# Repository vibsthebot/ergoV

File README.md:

# ergoV

A custom ergonomic split keyboard powered by a nrf52840 and PG1316S switches. At under 8 millimeters thick, this keyboard is extremly thin and portable. 

## Features
* Battery Charging
* USB C
* Bluetooth

## PCB 

## Schematic

Designed in [KiCAD](https://kicanvas.org/?github=https%3A%2F%2Fgithub.com%2Fvibsthebot%2FergoV%2Ftree%2Fmain%2Fsrc%2Fleft) and [Onshape](https://cad.onshape.com/documents/23d341e5ba1096076f5e498a/w/17b9fcd4bdbd13d07aada607/e/fd0f7eacd049861961437f33?renderMode=0&uiState=68cac4ba1e18efa2742f181c)

## BOM

| Item                                    | Quantity | Link                                                                                                         | Price (each) |
|------------------------------------------|----------|--------------------------------------------------------------------------------------------------------------|--------------|
| 301540 batteries                        | 2        | [AliExpress](https://www.aliexpress.com/i/2255800173650652.html)                                             | $6.10        |
| PCB (JLCPCB)                            | 2        | -                                                                                                            | $8.40        |
| LCSC parts                              | -        | -                                                                                                            | $50.00       |
| PG1316S switches (10 pack)              | 4 packs  | [HolyKeebs](https://holykeebs.com/products/kailh-pg1316s-butterfly-switch-10-pack)                           | $7.50        |
| PG1316S keycaps (10 pack)               | 4 packs  | [HolyKeebs](https://holykeebs.com/products/kailh-pg1316s-keycaps)                                            | $4.50        |
| **Total**                               |          |                                                                                                              | **$129.60**  |

**Total estimated cost:** $129.60

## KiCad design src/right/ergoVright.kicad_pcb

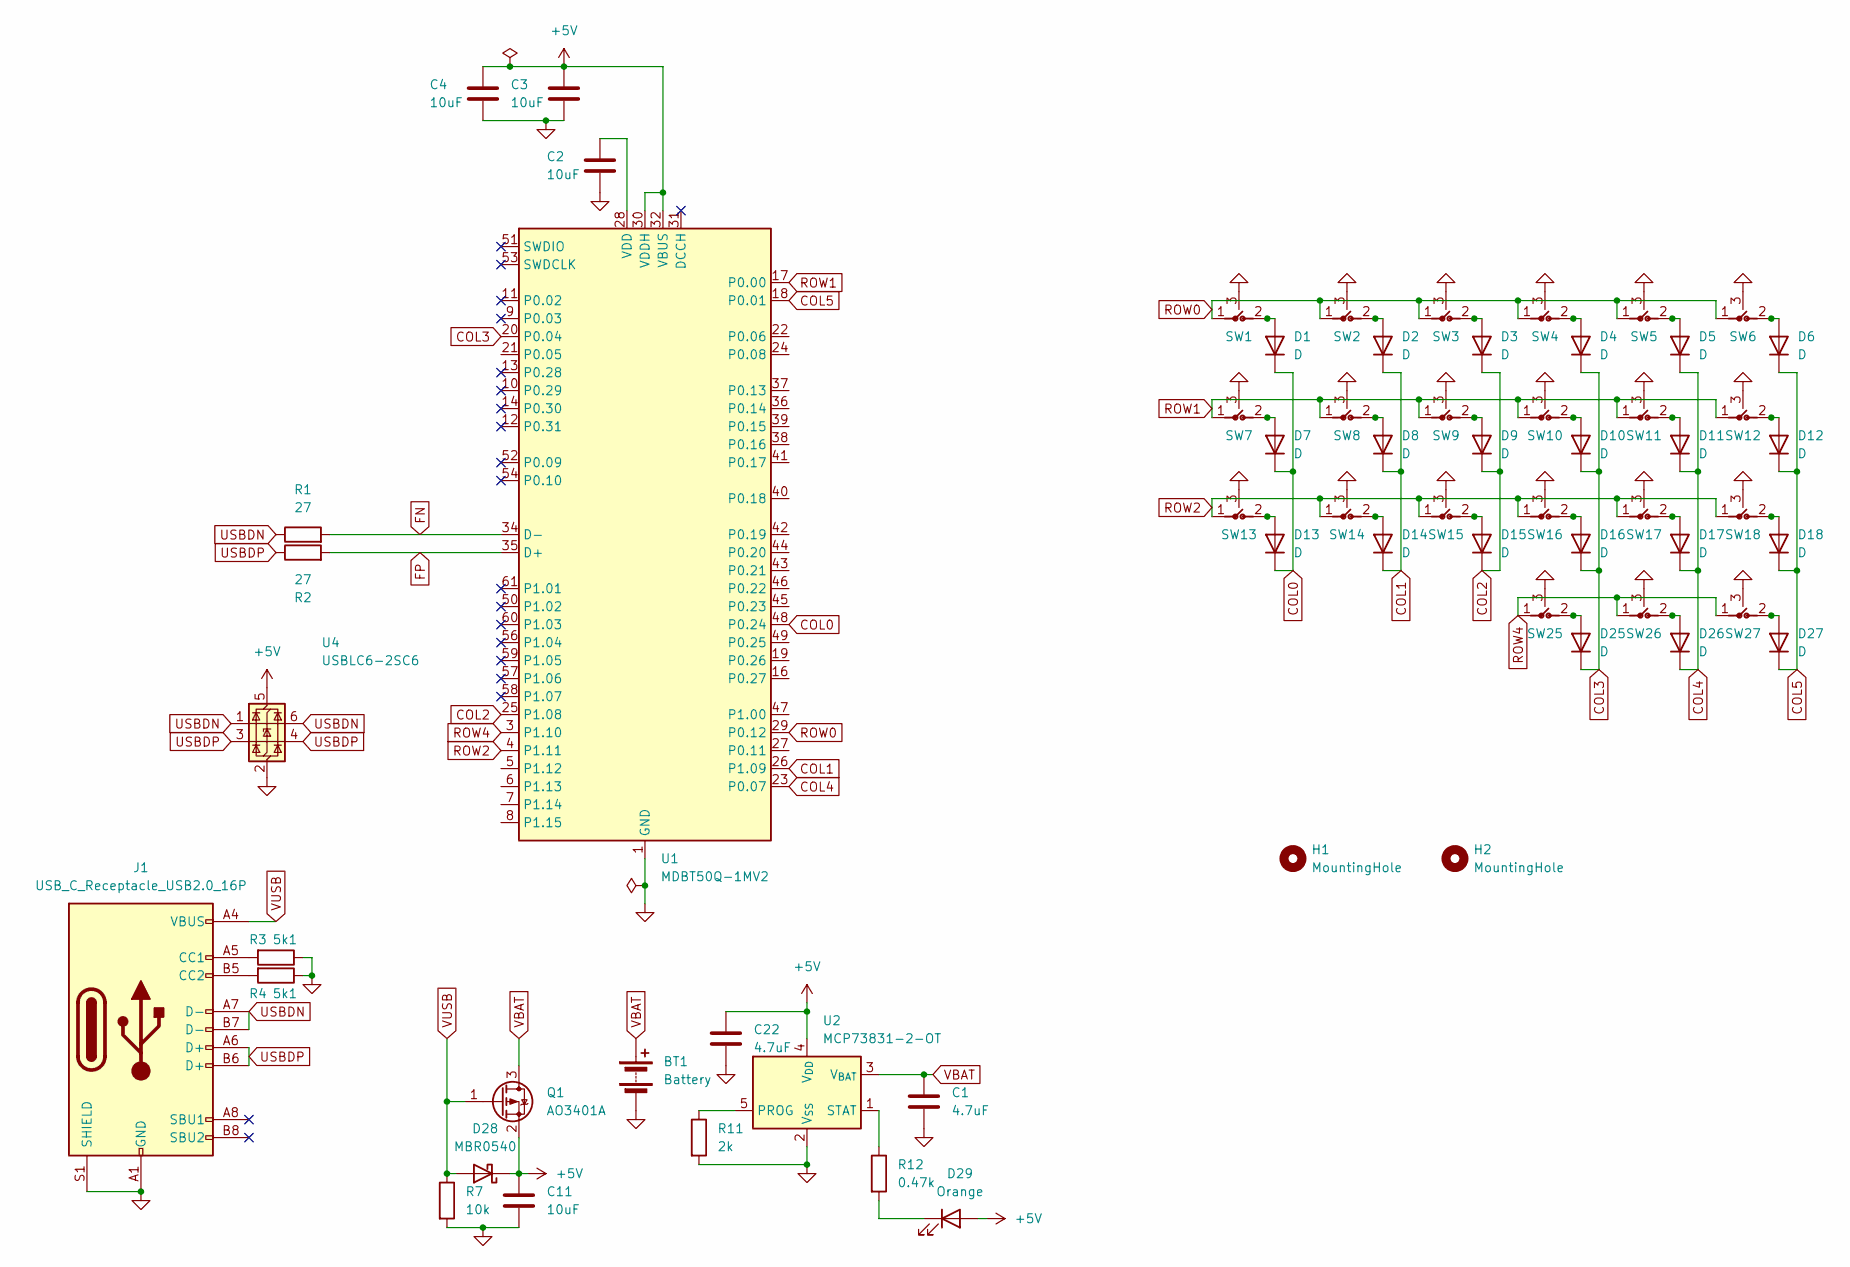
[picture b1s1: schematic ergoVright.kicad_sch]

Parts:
BT1: Battery; JST_PH_S2B-PH-K_1x02_P2.00mm_Horizontal
C1, C22: 4.7uF; C_0603_1608Metric; LCSC C19666
C2, C3, C4, C11: 10uF; C_0603_1608Metric; LCSC C19702
D1, D2, D3, D4, D5, D6, D7, D8, D9, D10, D11, D12, D13, D14, D15, D16, D17, D18, D25, D26, D27: D; Diode_SOD-123; LCSC C81598
D28: MBR0540; D_SOD-123; LCSC C77337
D29: Orange; LED_0805_2012Metric; LCSC C434437
H1, H2: MountingHole; MountingHole_2.7mm_M2.5
J1: USB_C_Receptacle_USB2.0_16P; USB_C_Receptacle_G-Switch_GT-USB-7010ASV; LCSC C67380
Q1: AO3401A; SOT-23; LCSC C306862
R1, R2: 27; R_0402_1005Metric; LCSC C25100
R3, R4: 5k1; R_0603_1608Metric; LCSC C23186
R7: 10k; R_0603_1608Metric; LCSC C25804
R11: 2k; R_0603_1608Metric; LCSC C22975
R12: 0.47k; R_0603_1608Metric; LCSC C23179
SW1, SW2, SW3, SW4, SW5, SW6, SW7, SW8, SW9, SW10, SW11, SW12, SW13, SW14, SW15, SW16, SW17, SW18, SW25, SW26, SW27: SW_Push_3pin_GND; CPG1316S01D02_kailhspecsheet_mikefive
U1: MDBT50Q-1MV2; Raytac_MDBT50Q; LCSC C14879
U2: MCP73831-2-OT; SOT-23-5; LCSC C5180249
U4: USBLC6-2SC6; SOT-23-6; LCSC C67380

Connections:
+5V: C3.1, C4.1, C11.1, C22.1, D28.1 (K), D29.2 (A), Q1.2 (S), U1.30 (VDDH), U1.32 (VBUS), U2.4 (V_{DD}), U4.5 (VBUS)
COL0: D1.1 (K), D7.1 (K), D13.1 (K), U1.48 (P0.24)
COL1: D2.1 (K), D8.1 (K), D14.1 (K), U1.26 (P1.09)
COL2: D3.1 (K), D9.1 (K), D15.1 (K), U1.25 (P1.08)
COL3: D4.1 (K), D10.1 (K), D16.1 (K), D25.1 (K), U1.20 (P0.04)
COL4: D5.1 (K), D11.1 (K), D17.1 (K), D26.1 (K), U1.23 (P0.07)
COL5: D6.1 (K), D12.1 (K), D18.1 (K), D27.1 (K), U1.18 (P0.01)
FN: R1.2, U1.34 (D-)
FP: R2.2, U1.35 (D+)
GND: BT1.2 (-), C1.2, C2.2, C3.2, C4.2, C11.2, C22.2, J1.A1 (GND), J1.A12 (GND), J1.B1 (GND), J1.B12 (GND), J1.S1 (SHIELD), R3.1, R4.1, R7.2, R11.2, SW1.3, SW2.3, SW3.3, SW4.3, SW5.3, SW6.3, SW7.3, SW8.3, SW9.3, SW10.3, SW11.3, SW12.3, SW13.3, SW14.3, SW15.3, SW16.3, SW17.3, SW18.3, SW25.3, SW26.3, SW27.3, U1.1 (GND), U1.2 (GND), U1.15 (GND), U1.33 (GND), U1.55 (GND), U2.2 (V_{SS}), U4.2 (GND)
unnamed: D1.2 (A), SW1.2
unnamed: D2.2 (A), SW2.2
unnamed: D3.2 (A), SW3.2
unnamed: D4.2 (A), SW4.2
unnamed: D5.2 (A), SW5.2
unnamed: D6.2 (A), SW6.2
unnamed: D7.2 (A), SW7.2
unnamed: D8.2 (A), SW8.2
unnamed: D9.2 (A), SW9.2
unnamed: D10.2 (A), SW10.2
unnamed: D11.2 (A), SW11.2
unnamed: D12.2 (A), SW12.2
unnamed: D13.2 (A), SW13.2
unnamed: D14.2 (A), SW14.2
unnamed: D15.2 (A), SW15.2
unnamed: D16.2 (A), SW16.2
unnamed: D17.2 (A), SW17.2
unnamed: D18.2 (A), SW18.2
unnamed: D25.2 (A), SW25.2
unnamed: D26.2 (A), SW26.2
unnamed: D27.2 (A), SW27.2
unnamed: D29.1 (K), R12.2
unnamed: J1.A5 (CC1), R3.2
unnamed: J1.B5 (CC2), R4.2
unnamed: C2.1, U1.28 (VDD)
unnamed: R11.1, U2.5 (PROG)
unnamed: R12.1, U2.1 (STAT)
ROW0: SW1.1, SW2.1, SW3.1, SW4.1, SW5.1, SW6.1, U1.29 (P0.12)
ROW1: SW7.1, SW8.1, SW9.1, SW10.1, SW11.1, SW12.1, U1.17 (P0.00)
ROW2: SW13.1, SW14.1, SW15.1, SW16.1, SW17.1, SW18.1, U1.4 (P1.11)
ROW4: SW25.1, SW26.1, SW27.1, U1.3 (P1.10)
USBDN: J1.A7 (D-), J1.B7 (D-), R1.1, U4.1 (I/O1), U4.6 (I/O1)
USBDP: J1.A6 (D+), J1.B6 (D+), R2.1, U4.3 (I/O2), U4.4 (I/O2)
VBAT: BT1.1 (+), C1.1, Q1.3 (D), U2.3 (V_{BAT})
VUSB: D28.2 (A), J1.A4 (VBUS), J1.A9 (VBUS), J1.B4 (VBUS), J1.B9 (VBUS), Q1.1 (G), R7.1

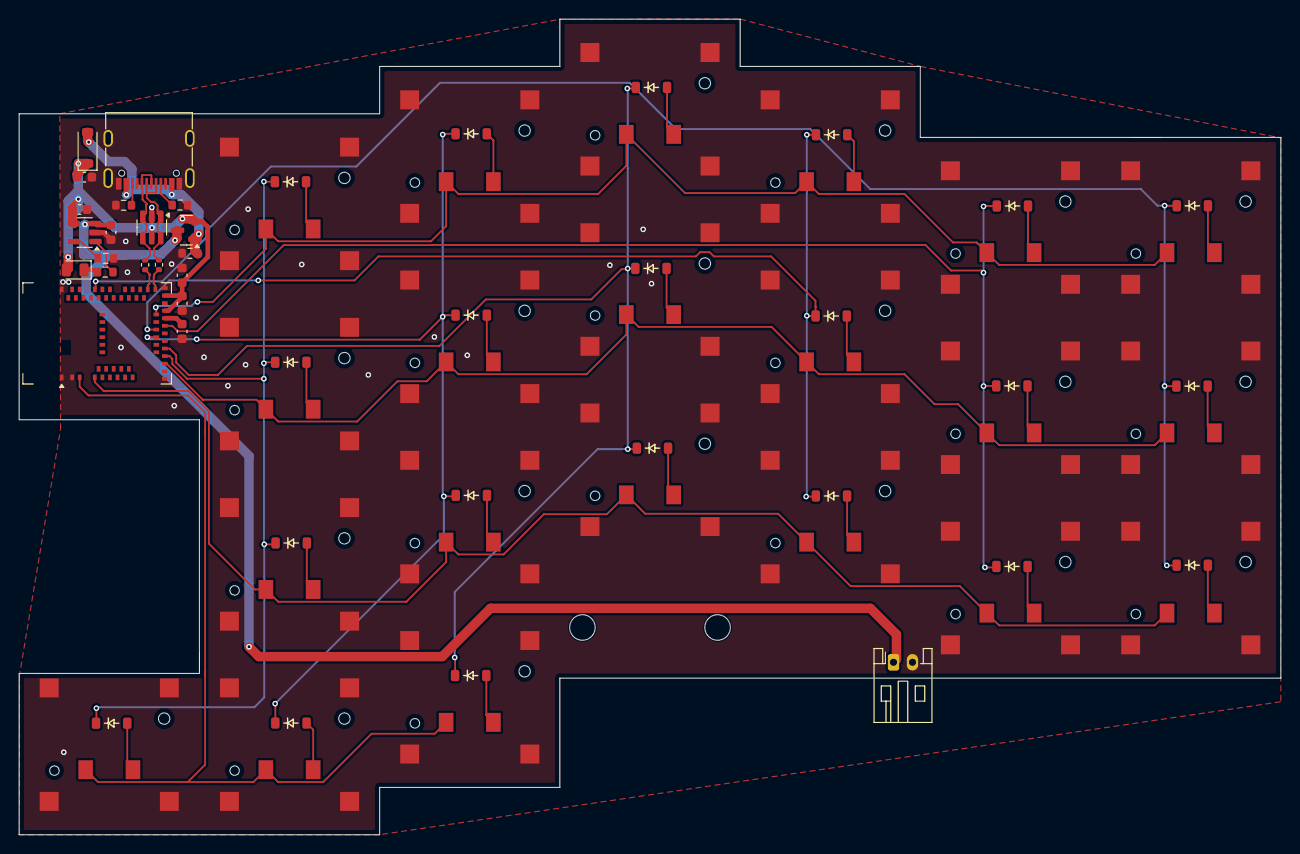
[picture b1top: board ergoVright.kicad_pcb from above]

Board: 2 copper layers, 133.3 x 86.2 mm, 65 parts (0 on the bottom side), 45 nets.

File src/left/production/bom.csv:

Designator,Footprint,Quantity,Value,LCSC Part #
BT1,JST_PH_S2B-PH-K_1x02_P2.00mm_Horizontal,1,Battery,C265016
"C1, C22",0402,2,4.7uF,C1779
"C11, C2, C3, C4",0402,4,10uF,C15525
"D1, D10, D11, D12, D13, D14, D15, D16, D17, D18, D2, D25, D26, D27, D3, D4, D5, D6, D7, D8, D9",Diode_SOD-123,21,D,C81598
D28,D_SOD-123,1,MBR0540,C77337
D29,0805,1,Orange,C434437
J1,USB_C_Receptacle_G-Switch_GT-USB-7010ASV,1,USB_C_Receptacle_USB2.0_16P,C67380
Q1,SOT-23,1,AO3401A,C306862
"R1, R2",0402,2,27,C25100
R11,0402,1,2k,C17604
R12,0402,1,0.47k,C17710
"R3, R4",0402,2,5k1,C25905
R7,0402,1,10k,C17414
"SW1, SW10, SW11, SW12, SW13, SW14, SW15, SW16, SW17, SW18, SW2, SW25, SW26, SW27, SW3, SW4, SW5, SW6, SW7, SW8, SW9",CPG1316S01D02_kailhspecsheet_mikefive,21,SW_Push_3pin_GND,
U1,Raytac_MDBT50Q,1,MDBT50Q-1MV2,
U2,SOT-23-5,1,MCP73831-2-OT,C14879
U4,SOT-23-6,1,USBLC6-2SC6,C5180249

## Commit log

2025-09-05 Finished keyboard!
2025-09-15 Finished pcb, started working on readme
2025-09-19 Finished readme and updated the pcb
2025-09-20 Finished readme
2025-09-20 Added cad
